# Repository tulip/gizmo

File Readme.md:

# Micro Word Clock v2

## Arduino IDE setup (must do for programming with AVRISP and Arduino)
- Download the latest version of the [Arduino IDE](https://www.arduino.cc/en/main/software)
- `cd ~/Documents/Arduino && mkdir hardware`
- cd into `hardware` clone [this repository](https://github.com/carlosefr/atmega) into it
- Restart the Arduino IDE, you should see `Tools > Board > ATMega328` and some other things show up

## Upload instructions with AVRISP MKII programmer

##### Burning the bootloader
- Plug in the Gizmo so that it is powered externally - the AVRISP MKII will **not** work if it is not powered externally
- Plug in the AVRISP, select `Tools > Programmer > AVRISP mkII`
- Plug in ICSP header from AVRISP to ICSP header on Gizmo (ICSP labels on Gizmo are on back of board)
- Select `Tools > Board > ATmega328/328p`
- Select `Tools > Processor > ATmega328p`
- Select `Tools > Clock > Internal 8 MHz`
- If everything is good, you should see a green light at the bottom of the programmer.
- Select `Tools > Burn Bootloader`
- If the programmer is working, you should see a second green light flash as it is programming. 

##### Uploading sketch
- Open `MicroWordClock2-Arduino.ino` in Arduino IDE
- Select `Sketch > Upload Using Programmer`

## Upload instructions with Arduino Uno

##### Setting up the Arduino Uno as an ISP
- Plug in the Arduino, select `Tools > Programmer > Arduino as ISP` and `Tools > Board > Arduino/Genuino Uno`
- Select `File > Examples > ArduinoISP` and see a new script open
- Make sure that the correct port is selected in `Tools > Port`
- On the top left corner of the window, select upload

##### Burning the Bootloader
- Wire up the Arduino to Gizmo's ICSP header, but make sure to wire up power last (Gizmo has the standard ICSP header configuration). Use the following wiring:

| Arduino pin | ICSP header pin |
|-------------|-----------------|
| 10          | RESET           |
| 11          | MOSI            |
| 12          | MISO            |
| 13          | SCK             |
| 5 V         | VCC             |
| GND         | GND             |

- Connect a 10uF capacitor between Arduino's RESET pin and GND
- Select `Tools > Board > ATmega328/328p`
- Select `Tools > Processor > ATmega328p`
- Select `Tools > Clock > Internal 8 MHz`
- Select `Tools > Burn Bootloader`

##### Uploading sketch
- Open `MicroWordClock2-Arduino.ino` in Arduino IDE
- With cap still plugged in and same `Tools` settings as before, select `Sketch > Upload Using Programmer`
- The TX and RX LEDs on the Arduino should start blinking, all LEDs on the Gizmo board should light up initially, then the board should be good to go

##### Troubleshooting 
- Make sure the correct option is selected under `Tools > Board` - should be Arduino Uno only when uploading ISP sketch
- Make sure the connections to the 10uF cap are good - I plugged it into a breadboard and used jumper wires to connect
- If nothing's working, try power cycling

## Setting the time 
- Once the sketch is uploaded, unplug the Arduino/programmer and plug in Gizmo's independent power supply
- Hold down SW1 until words start blinking. To cycle through "quarter past", "half past", etc., press SW1 the number of minutes you want to increment past the time designator
- To set the hour, hold down SW1 again until the current hour starts blinking and cycle through. Once you're done, hold down SW1 until only one LED blinks again

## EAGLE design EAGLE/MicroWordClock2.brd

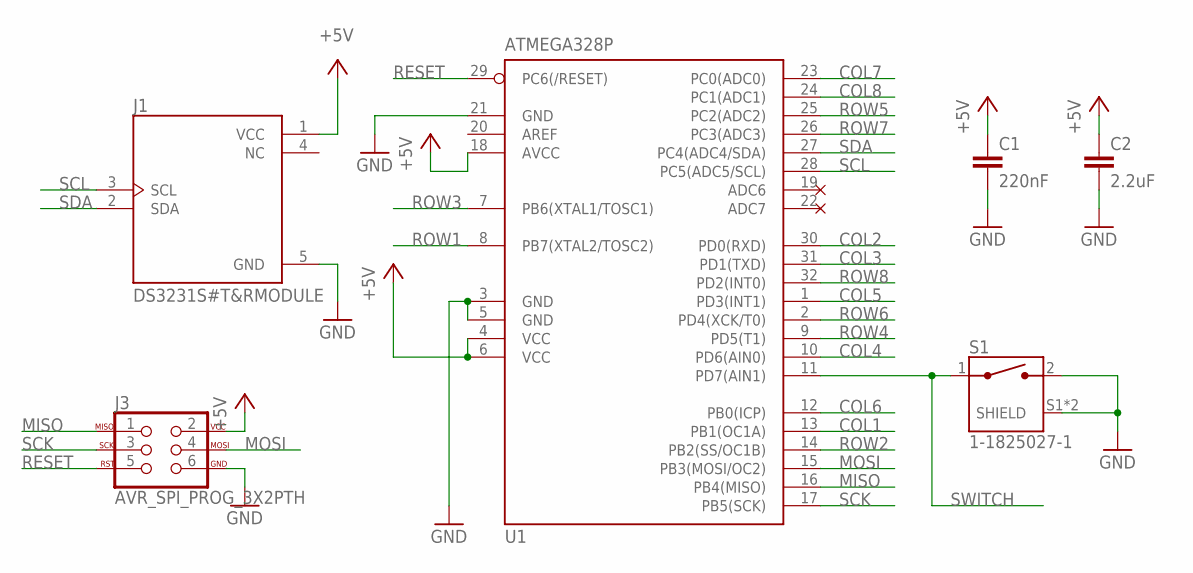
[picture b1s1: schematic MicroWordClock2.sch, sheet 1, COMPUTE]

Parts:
C1: 220nF; C0603
C2: 2.2uF; C0603
J1: DS3231S#T&RMODULE; 1X05
J3: AVR_SPI_PROG_3X2PTH; 2X3
S1: 1-1825027-1; SW_1-1825027-1
U1: ATMEGA328P; TQFP32-08

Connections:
+5V: C1.1, C2.1, J1.1 (VCC), J3.2, U1.4 (VCC), U1.6 (VCC), U1.18 (AVCC); also elsewhere on the board
COL1: U1.13 (PB1(OC1A)); also elsewhere on the board
COL2: U1.30 (PD0(RXD)); also elsewhere on the board
COL3: U1.31 (PD1(TXD)); also elsewhere on the board
COL4: U1.10 (PD6(AIN0)); also elsewhere on the board
COL5: U1.1 (PD3(INT1)); also elsewhere on the board
COL6: U1.12 (PB0(ICP)); also elsewhere on the board
COL7: U1.23 (PC0(ADC0)); also elsewhere on the board
COL8: U1.24 (PC1(ADC1)); also elsewhere on the board
GND: C1.2, C2.2, J1.5 (GND), J3.6, S1.2, S1.S1 (SHIELD), S1.S2 (SHIELD), U1.3 (GND), U1.5 (GND), U1.21 (GND); also elsewhere on the board
MISO: J3.1, U1.16 (PB4(MISO))
MOSI: J3.4, U1.15 (PB3(MOSI/OC2))
RESET: J3.5, U1.29 (PC6(/RESET))
ROW1: U1.8 (PB7(XTAL2/TOSC2)); also elsewhere on the board
ROW2: U1.14 (PB2(SS/OC1B)); also elsewhere on the board
ROW3: U1.7 (PB6(XTAL1/TOSC1)); also elsewhere on the board
ROW4: U1.9 (PD5(T1)); also elsewhere on the board
ROW5: U1.25 (PC2(ADC2)); also elsewhere on the board
ROW6: U1.2 (PD4(XCK/T0)); also elsewhere on the board
ROW7: U1.26 (PC3(ADC3)); also elsewhere on the board
ROW8: U1.32 (PD2(INT0)); also elsewhere on the board
SCK: J3.3, U1.17 (PB5(SCK))
SCL: J1.3 (SCL), U1.28 (PC5(ADC5/SCL))
SDA: J1.2 (SDA), U1.27 (PC4(ADC4/SDA))
SWITCH: S1.1, U1.11 (PD7(AIN1)); also elsewhere on the board

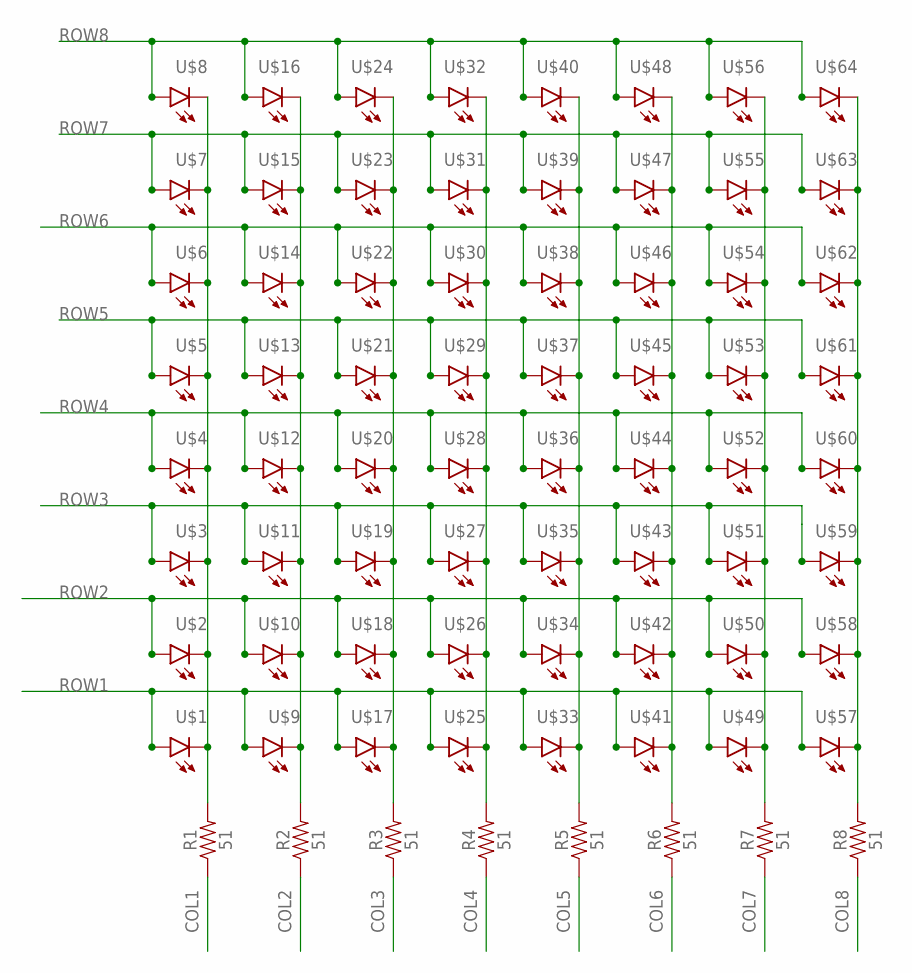
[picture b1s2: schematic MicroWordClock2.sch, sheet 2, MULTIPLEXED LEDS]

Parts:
R1, R2, R3, R4, R5, R6, R7, R8: 51; 0603
U$1, U$2, U$3, U$4, U$5, U$6, U$7, U$8, U$9, U$10, U$11, U$12, U$13, U$14, U$15, U$16, U$17, U$18, U$19, U$20, U$21, U$22, U$23, U$24, U$25, U$26, U$27, U$28, U$29, U$30, U$31, U$32, U$33, U$34, U$35, U$36, U$37, U$38, U$39, U$40, U$41, U$42, U$43, U$44, U$45, U$46, U$47, U$48, U$49, U$50, U$51, U$52, U$53, U$54, U$55, U$56, U$57, U$58, U$59, U$60, U$61, U$62, U$63, U$64: WHITE; 1113(2835METRIC)

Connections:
COL1: R1.1; also elsewhere on the board
COL2: R2.1; also elsewhere on the board
COL3: R3.1; also elsewhere on the board
COL4: R4.1; also elsewhere on the board
COL5: R5.1; also elsewhere on the board
COL6: R6.1; also elsewhere on the board
COL7: R7.1; also elsewhere on the board
COL8: R8.1; also elsewhere on the board
EE: R8.2, U$57.CATHODE (C), U$58.CATHODE (C), U$59.CATHODE (C), U$60.CATHODE (C), U$61.CATHODE (C), U$62.CATHODE (C), U$63.CATHODE (C), U$64.CATHODE (C)
unnamed: R3.2, U$17.CATHODE (C), U$18.CATHODE (C), U$19.CATHODE (C), U$20.CATHODE (C), U$21.CATHODE (C), U$22.CATHODE (C), U$23.CATHODE (C), U$24.CATHODE (C)
unnamed: R4.2, U$25.CATHODE (C), U$26.CATHODE (C), U$27.CATHODE (C), U$28.CATHODE (C), U$29.CATHODE (C), U$30.CATHODE (C), U$31.CATHODE (C), U$32.CATHODE (C)
unnamed: R5.2, U$33.CATHODE (C), U$34.CATHODE (C), U$35.CATHODE (C), U$36.CATHODE (C), U$37.CATHODE (C), U$38.CATHODE (C), U$39.CATHODE (C), U$40.CATHODE (C)
unnamed: R6.2, U$41.CATHODE (C), U$42.CATHODE (C), U$43.CATHODE (C), U$44.CATHODE (C), U$45.CATHODE (C), U$46.CATHODE (C), U$47.CATHODE (C), U$48.CATHODE (C)
unnamed: R7.2, U$49.CATHODE (C), U$50.CATHODE (C), U$51.CATHODE (C), U$52.CATHODE (C), U$53.CATHODE (C), U$54.CATHODE (C), U$55.CATHODE (C), U$56.CATHODE (C)
unnamed: R1.2, U$1.CATHODE (C), U$2.CATHODE (C), U$3.CATHODE (C), U$4.CATHODE (C), U$5.CATHODE (C), U$6.CATHODE (C), U$7.CATHODE (C), U$8.CATHODE (C)
unnamed: R2.2, U$9.CATHODE (C), U$10.CATHODE (C), U$11.CATHODE (C), U$12.CATHODE (C), U$13.CATHODE (C), U$14.CATHODE (C), U$15.CATHODE (C), U$16.CATHODE (C)
ROW1: U$1.ANODE (A), U$9.ANODE (A), U$17.ANODE (A), U$25.ANODE (A), U$33.ANODE (A), U$41.ANODE (A), U$49.ANODE (A), U$57.ANODE (A); also elsewhere on the board
ROW2: U$2.ANODE (A), U$10.ANODE (A), U$18.ANODE (A), U$26.ANODE (A), U$34.ANODE (A), U$42.ANODE (A), U$50.ANODE (A), U$58.ANODE (A); also elsewhere on the board
ROW3: U$3.ANODE (A), U$11.ANODE (A), U$19.ANODE (A), U$27.ANODE (A), U$35.ANODE (A), U$43.ANODE (A), U$51.ANODE (A), U$59.ANODE (A); also elsewhere on the board
ROW4: U$4.ANODE (A), U$12.ANODE (A), U$20.ANODE (A), U$28.ANODE (A), U$36.ANODE (A), U$44.ANODE (A), U$52.ANODE (A), U$60.ANODE (A); also elsewhere on the board
ROW5: U$5.ANODE (A), U$13.ANODE (A), U$21.ANODE (A), U$29.ANODE (A), U$37.ANODE (A), U$45.ANODE (A), U$53.ANODE (A), U$61.ANODE (A); also elsewhere on the board
ROW6: U$6.ANODE (A), U$14.ANODE (A), U$22.ANODE (A), U$30.ANODE (A), U$38.ANODE (A), U$46.ANODE (A), U$54.ANODE (A), U$62.ANODE (A); also elsewhere on the board
ROW7: U$7.ANODE (A), U$15.ANODE (A), U$23.ANODE (A), U$31.ANODE (A), U$39.ANODE (A), U$47.ANODE (A), U$55.ANODE (A), U$63.ANODE (A); also elsewhere on the board
ROW8: U$8.ANODE (A), U$16.ANODE (A), U$24.ANODE (A), U$32.ANODE (A), U$40.ANODE (A), U$48.ANODE (A), U$56.ANODE (A), U$64.ANODE (A); also elsewhere on the board

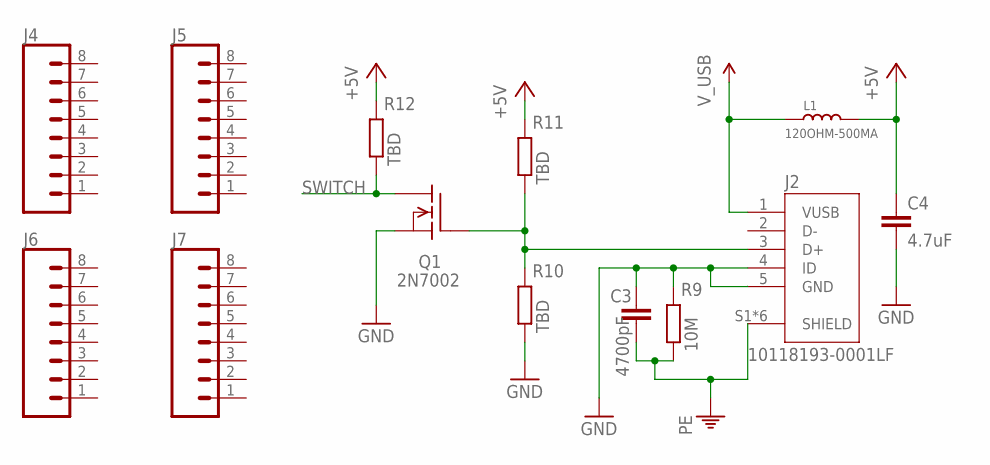
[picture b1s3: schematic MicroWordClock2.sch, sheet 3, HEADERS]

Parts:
C3: 4700pF; C0603
C4: 4.7uF; C0603
J2: 10118193-0001LF; FCI_10118193-0001LF
J4, J5, J6, J7: CONN_08"; 1X08
L1: 120OHM-500MA; L0603
Q1: 2N7002; SOT23
R9: 10M; R0603
R10, R11, R12: TBD; R0603

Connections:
+5V: C4.1, L1.2, R11.2, R12.2; also elsewhere on the board
GND: C3.1, C4.2, J2.4 (ID), J2.5 (GND), Q1.2 (S), R9.2, R10.1; also elsewhere on the board
unnamed: J2.3 (D+), Q1.1 (G), R10.2, R11.1
PE: C3.2, J2.S1 (SHIELD), J2.S2 (SHIELD), J2.S3 (SHIELD), J2.S4 (SHIELD), J2.S5 (SHIELD), J2.S6 (SHIELD), R9.1
SWITCH: Q1.3 (D), R12.1; also elsewhere on the board
V_USB: J2.1 (VUSB), L1.1

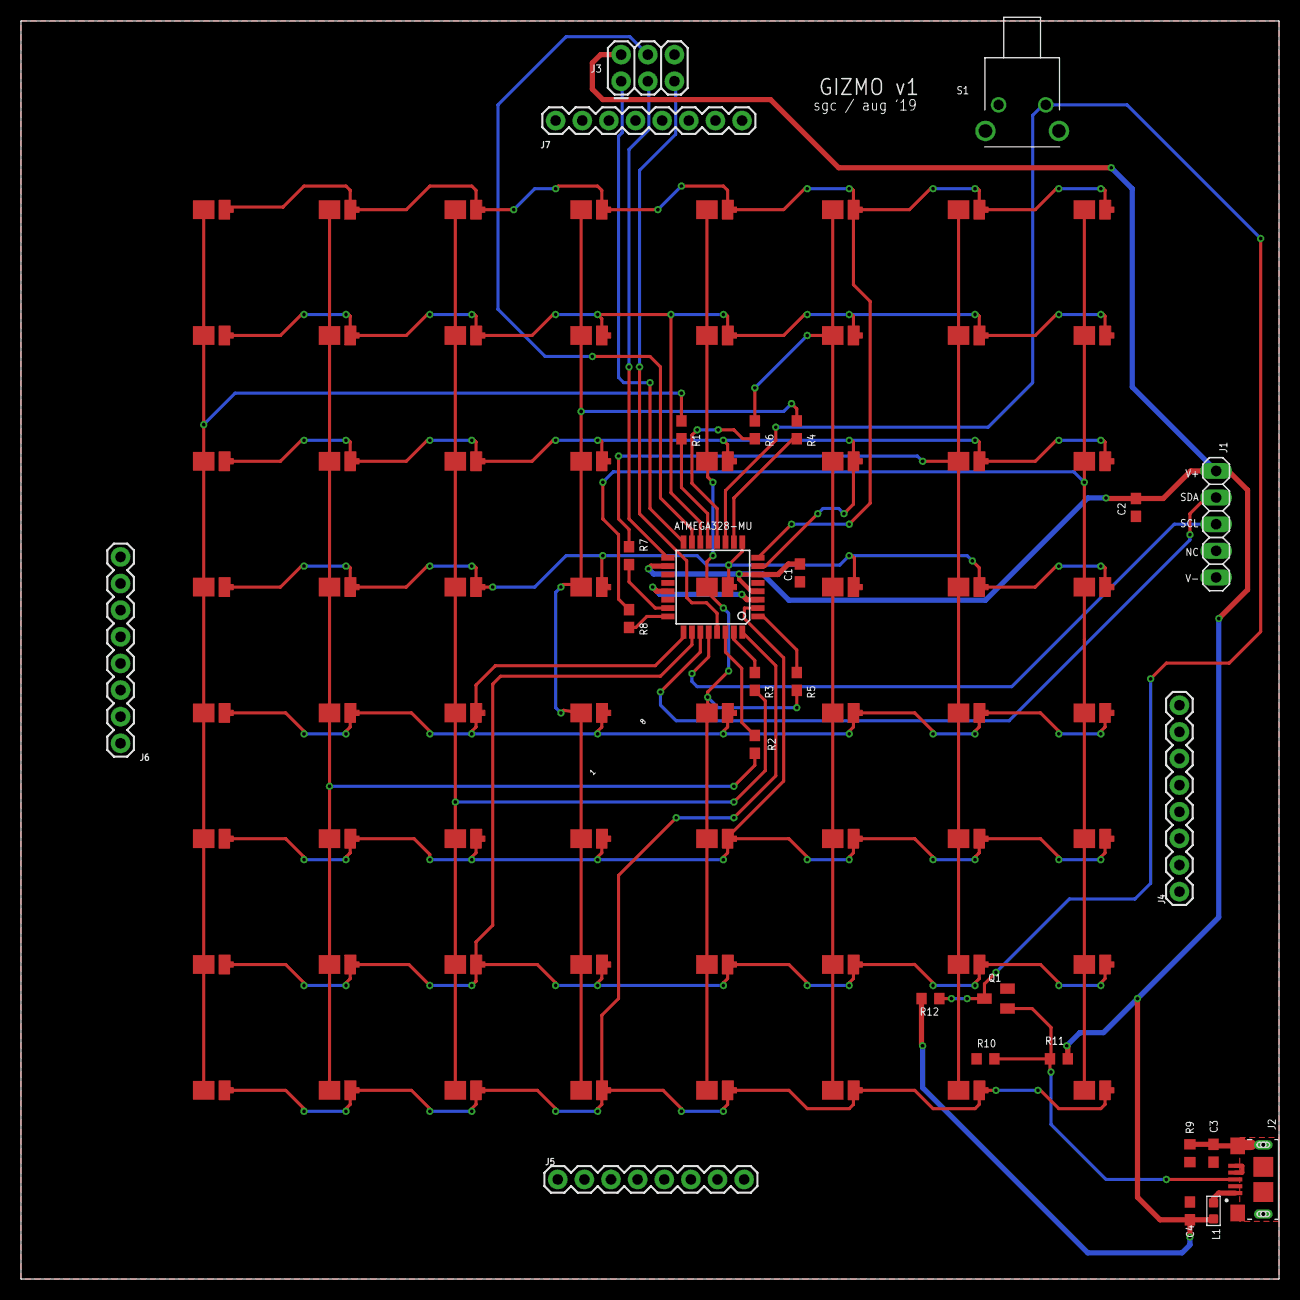
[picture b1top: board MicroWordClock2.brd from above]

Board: 2 copper layers, 120.0 x 120.0 mm, 91 parts (0 on the bottom side), 36 nets.

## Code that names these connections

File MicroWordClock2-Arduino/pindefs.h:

// Matching LED rows/columns to the matrix's pins
// to microcontroller ports to microcontroller pins
// to Arduino pin notation. Whew.

// PORTB: Digital pins (offset 8), PB6/PB7 are XTAL
// PORTC: Analog pins (no offset), PC6 is RESET, PC7 nonexistent
// PORTD: Digital pins (no offset)

// Pin definitions
#define PIN_BUTTON PD7

// Mapping Matrix Row/Col numbers to Matrix pins
#define MTX_ROW1 MTX_PIN9
#define MTX_ROW2 MTX_PIN14
#define MTX_ROW3 MTX_PIN8
#define MTX_ROW4 MTX_PIN12
#define MTX_ROW5 MTX_PIN1
#define MTX_ROW6 MTX_PIN7
#define MTX_ROW7 MTX_PIN2
#define MTX_ROW8 MTX_PIN5

#define MTX_COL1 MTX_PIN13
#define MTX_COL2 MTX_PIN3
#define MTX_COL3 MTX_PIN4
#define MTX_COL4 MTX_PIN10
#define MTX_COL5 MTX_PIN6
#define MTX_COL6 MTX_PIN11
#define MTX_COL7 MTX_PIN15
#define MTX_COL8 MTX_PIN16

#define MTX_PIN1  SIG_B1
#define MTX_PIN2  SIG_B2
#define MTX_PIN3  SIG_B3
#define MTX_PIN4  SIG_B4
#define MTX_PIN5  SIG_B5
#define MTX_PIN6  SIG_B6
#define MTX_PIN7  SIG_B7
#define MTX_PIN8  SIG_B8
#define MTX_PIN9  SIG_A8
#define MTX_PIN10 SIG_A7
#define MTX_PIN11 SIG_A6
#define MTX_PIN12 SIG_A5
#define MTX_PIN13 SIG_A4
#define MTX_PIN14 SIG_A3
#define MTX_PIN15 SIG_A2
#define MTX_PIN16 SIG_A1

#define SIG_A1  PC1
#define SIG_A2  PC0
#define SIG_A3  PB2
#define SIG_A4  PB1
#define SIG_A5  PD5
#define SIG_A6  PB0
#define SIG_A7  PD6
#define SIG_A8  PB7
#define SIG_B1  PC2
#define SIG_B2  PC3
#define SIG_B3  PD0
#define SIG_B4  PD1
#define SIG_B5  PD2
#define SIG_B6  PD3
#define SIG_B7  PD4
#define SIG_B8  PB6

#define PB0  8
#define PB1  9
#define PB2 10
#define PB3 11
#define PB4 12
#define PB5 13
#define PB6 A6 //XTAL1
#define PB7 A7 //XTAL2

#define PC0 A0
#define PC1 A1
#define PC2 A2
#define PC3 A3
#define PC4 A4
#define PC5 A5

#define PD0 0
#define PD1 1
#define PD2 2
#define PD3 3
#define PD4 4
#define PD5 5
#define PD6 6

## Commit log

2019-06-06 initial edits to update the existing layout with the same components as the original
2019-06-08 board with new footprints for switch, microusb and clock & complete routing
2019-06-08 fixing some stray wires, adding the tulip logo to the back
2019-06-08 adding tented vias + add additional board information text
2019-06-08 adding serial number landing area
2019-06-08 fixing some erc issues
2019-06-08 fixing the erc and drc of AVCC
2019-06-11 adding the dxf
2019-06-11 half way done with rerouting
2019-06-11 done rerouting everything except for power
2019-06-13 initial routing + pours. created a variant for the no pops
2019-06-13 fixing up the lettering
2019-06-13 Word Clock Face board added
2019-06-18 adding the LED library
2019-07-10 updated readme to include special bootloader instructs
2019-07-10 upadted code for tulip faceplate
2019-07-10 update readme with upload instructions
2019-07-11 fixed cols 2 and 3
2019-07-12 fixed lettering for 10
2019-07-12 updated readme w upload instructs
2019-07-12 added upload instructions .md
2019-07-12 markdown edits
2019-07-12 arduino 1.8.9 upload instruct edits
2019-07-12 link to upload instructs in readme
2019-08-14 Fixing initial bugs from V0 - pad sizes, SCL/SDA line switch see issue #4 for full list. Also added updated schematic"
2019-08-15 AVRISP upload instructions
2019-08-15 image edits
2019-08-29 Fixing flicker, changing default no-RTC-behavior to just be a flashing tulip
2019-08-29 added documentation about how to run the production tools and plug everything in
2019-08-29 Readme formatting
2019-08-29 Readme formatting and adding info about i2cset
2019-08-29 Some more readme formatting, updating the RTC programmer to initialize pins to power the RTC
2019-08-29 added bitwise and so that century/month works
2019-08-30 unfucked the blinkyness which was introduced by the addition of the RTC.read line in the display loop
2019-09-01 beginning to add functionality even if no RTC
2019-09-02 programming with no RTC working
2019-09-02 completed behavior w/o RTC is working - blinks when unset
2019-09-02 updating hex after testing
2019-09-03 adding the fuses doc
2019-09-03 updating the fuses in the the boards.txt file to be the ones we actually used, removing commented code
2019-09-03 removing the bash script to have more discrete PRs
2019-09-05 updating the Programming script to be a little more readable / better written
2019-09-06 updating word face to have smt headers
2019-09-12 adding the reset of the timing loop in the display loop to resolve flickering issue sabrina found
2019-09-12 added conditional to work with and without RTC
2019-09-12 committing the tulip face and fixing a header
2019-09-13 minimizing flicker
2019-09-13 adding the final hex file that flickers less due to the hack
2019-09-16 adding the build book for the release of assembly show
2019-09-16 removing old bb to reduce confusion
2019-09-16 fixing all of the shell-check errors and adding a blink on the B bank once programming completes
2019-11-05 adding an ProgramRTC.sh so the RPC considers it a successful exit
2024-01-24 Unpacking path, adding changes for Messe '24
2024-05-21 Updated after Production Run 2, Start of Production Run 3

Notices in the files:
parts and their libraries:
SparkFun-Resistors: Licensing: Creative Commons ShareAlike 4.0 International - https://creativecommons.org/licenses/by-sa/4.0
